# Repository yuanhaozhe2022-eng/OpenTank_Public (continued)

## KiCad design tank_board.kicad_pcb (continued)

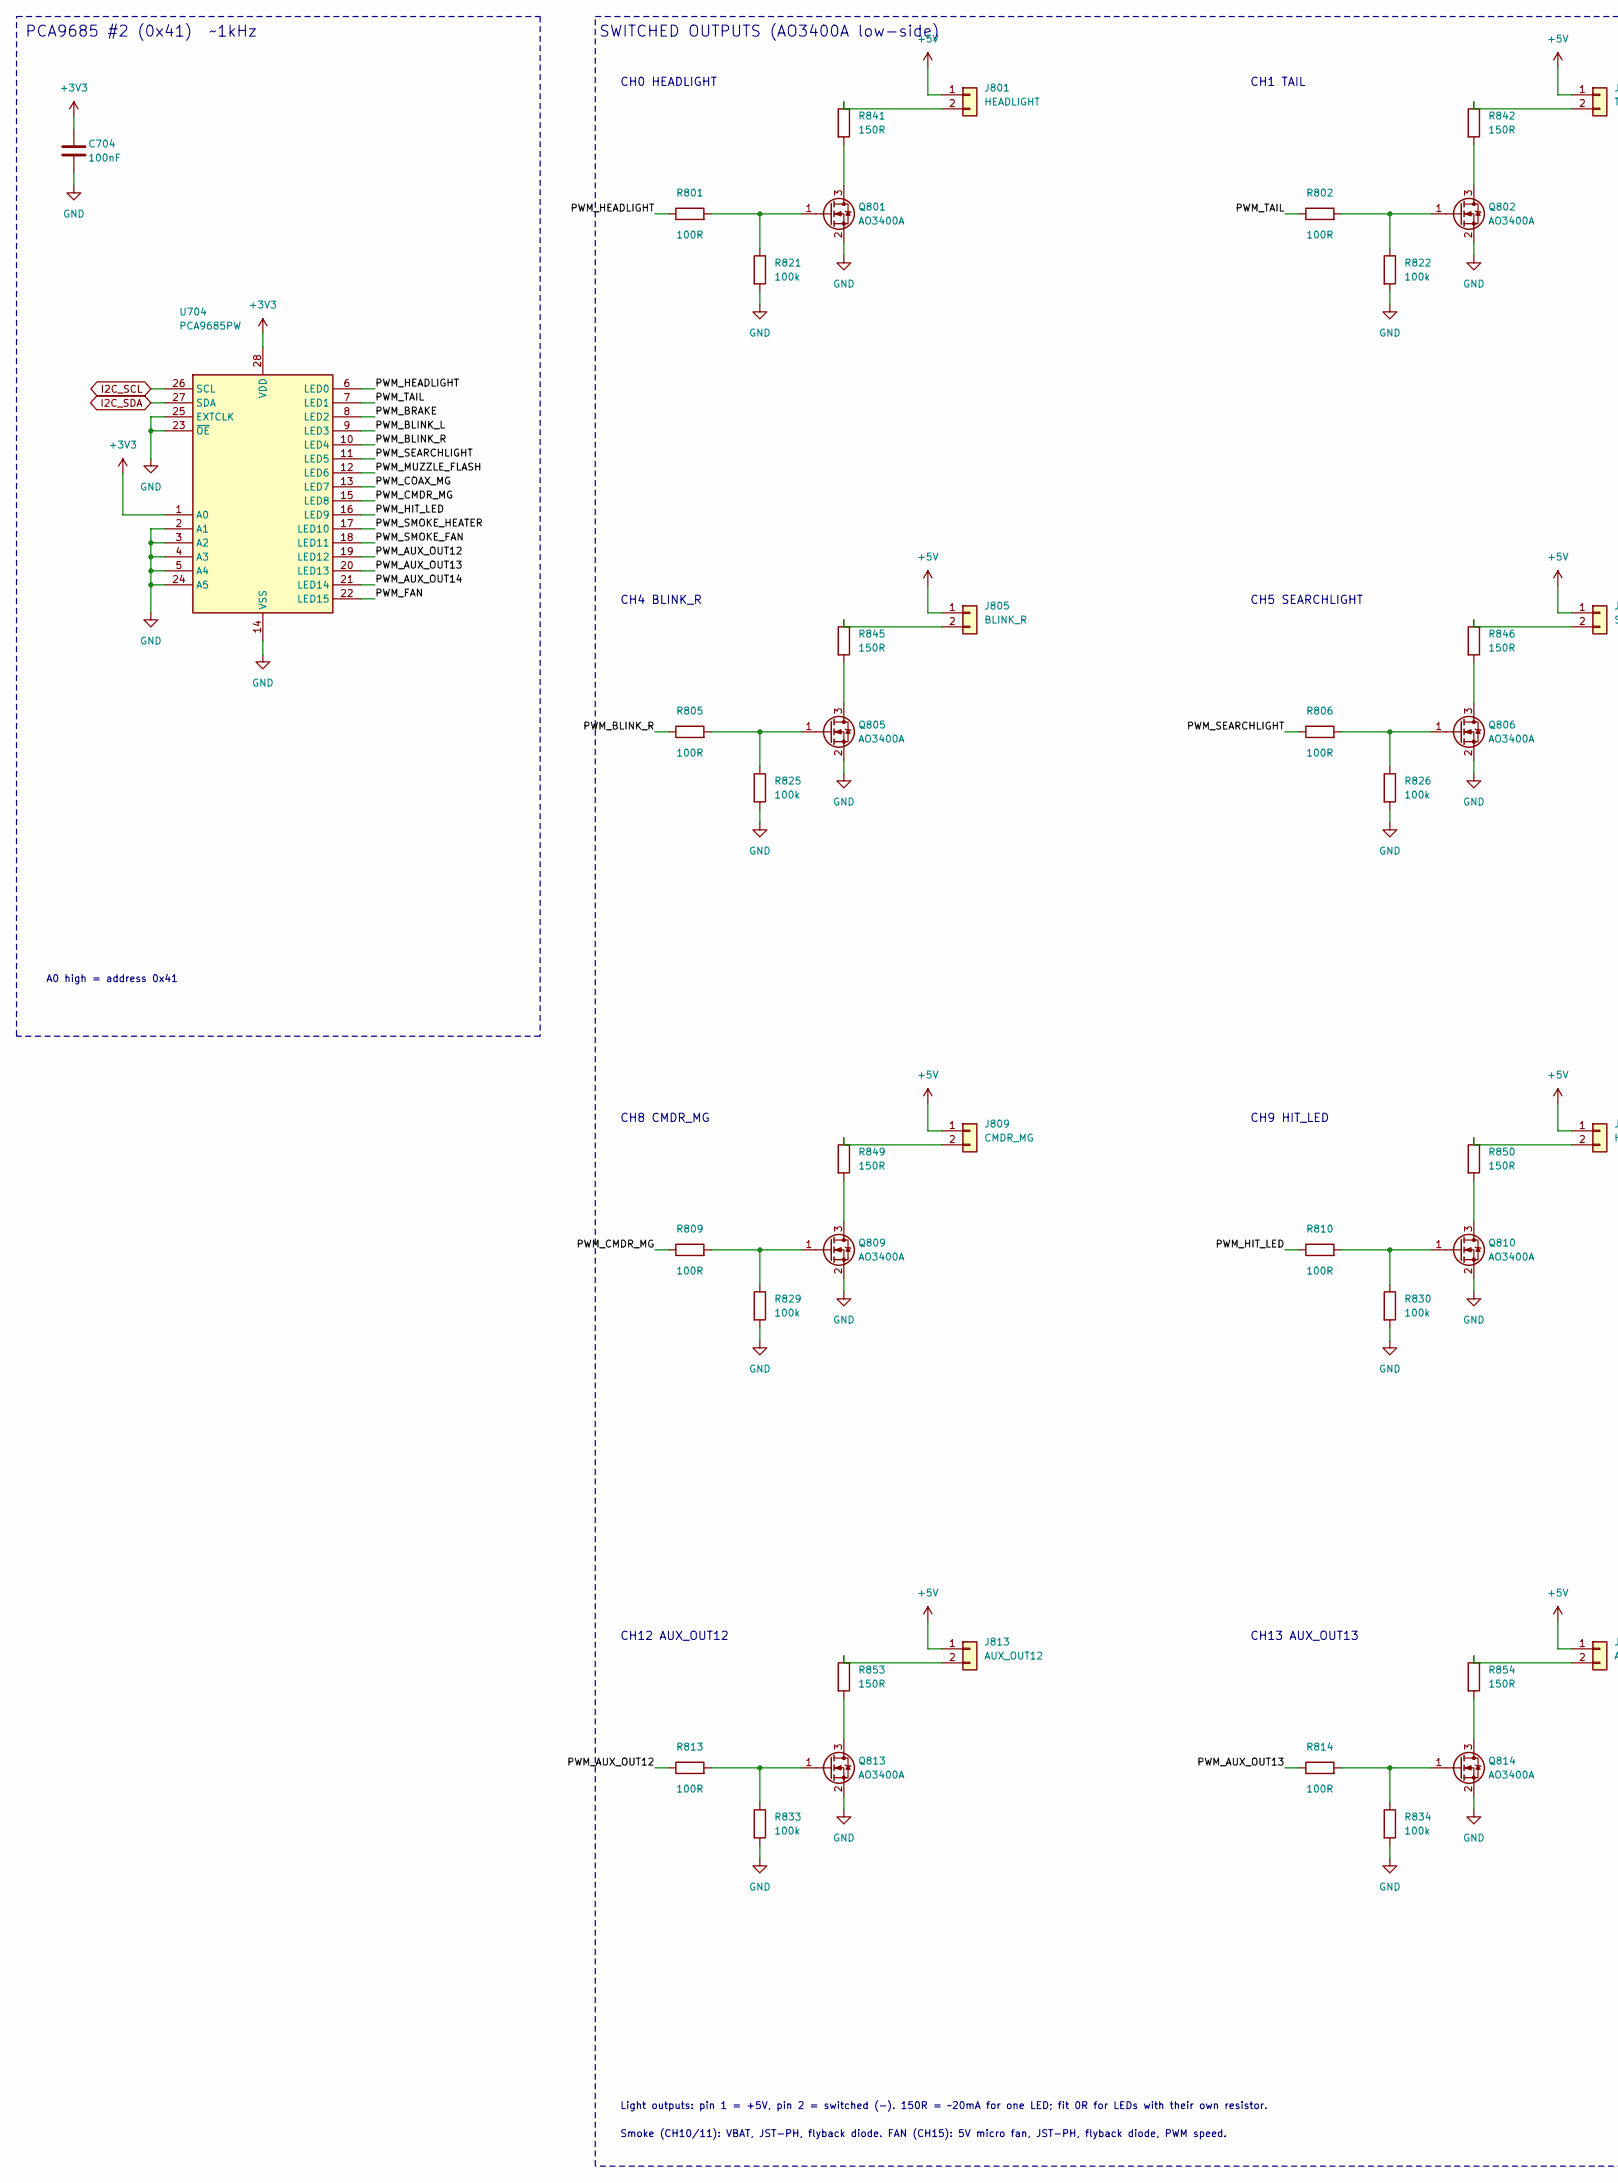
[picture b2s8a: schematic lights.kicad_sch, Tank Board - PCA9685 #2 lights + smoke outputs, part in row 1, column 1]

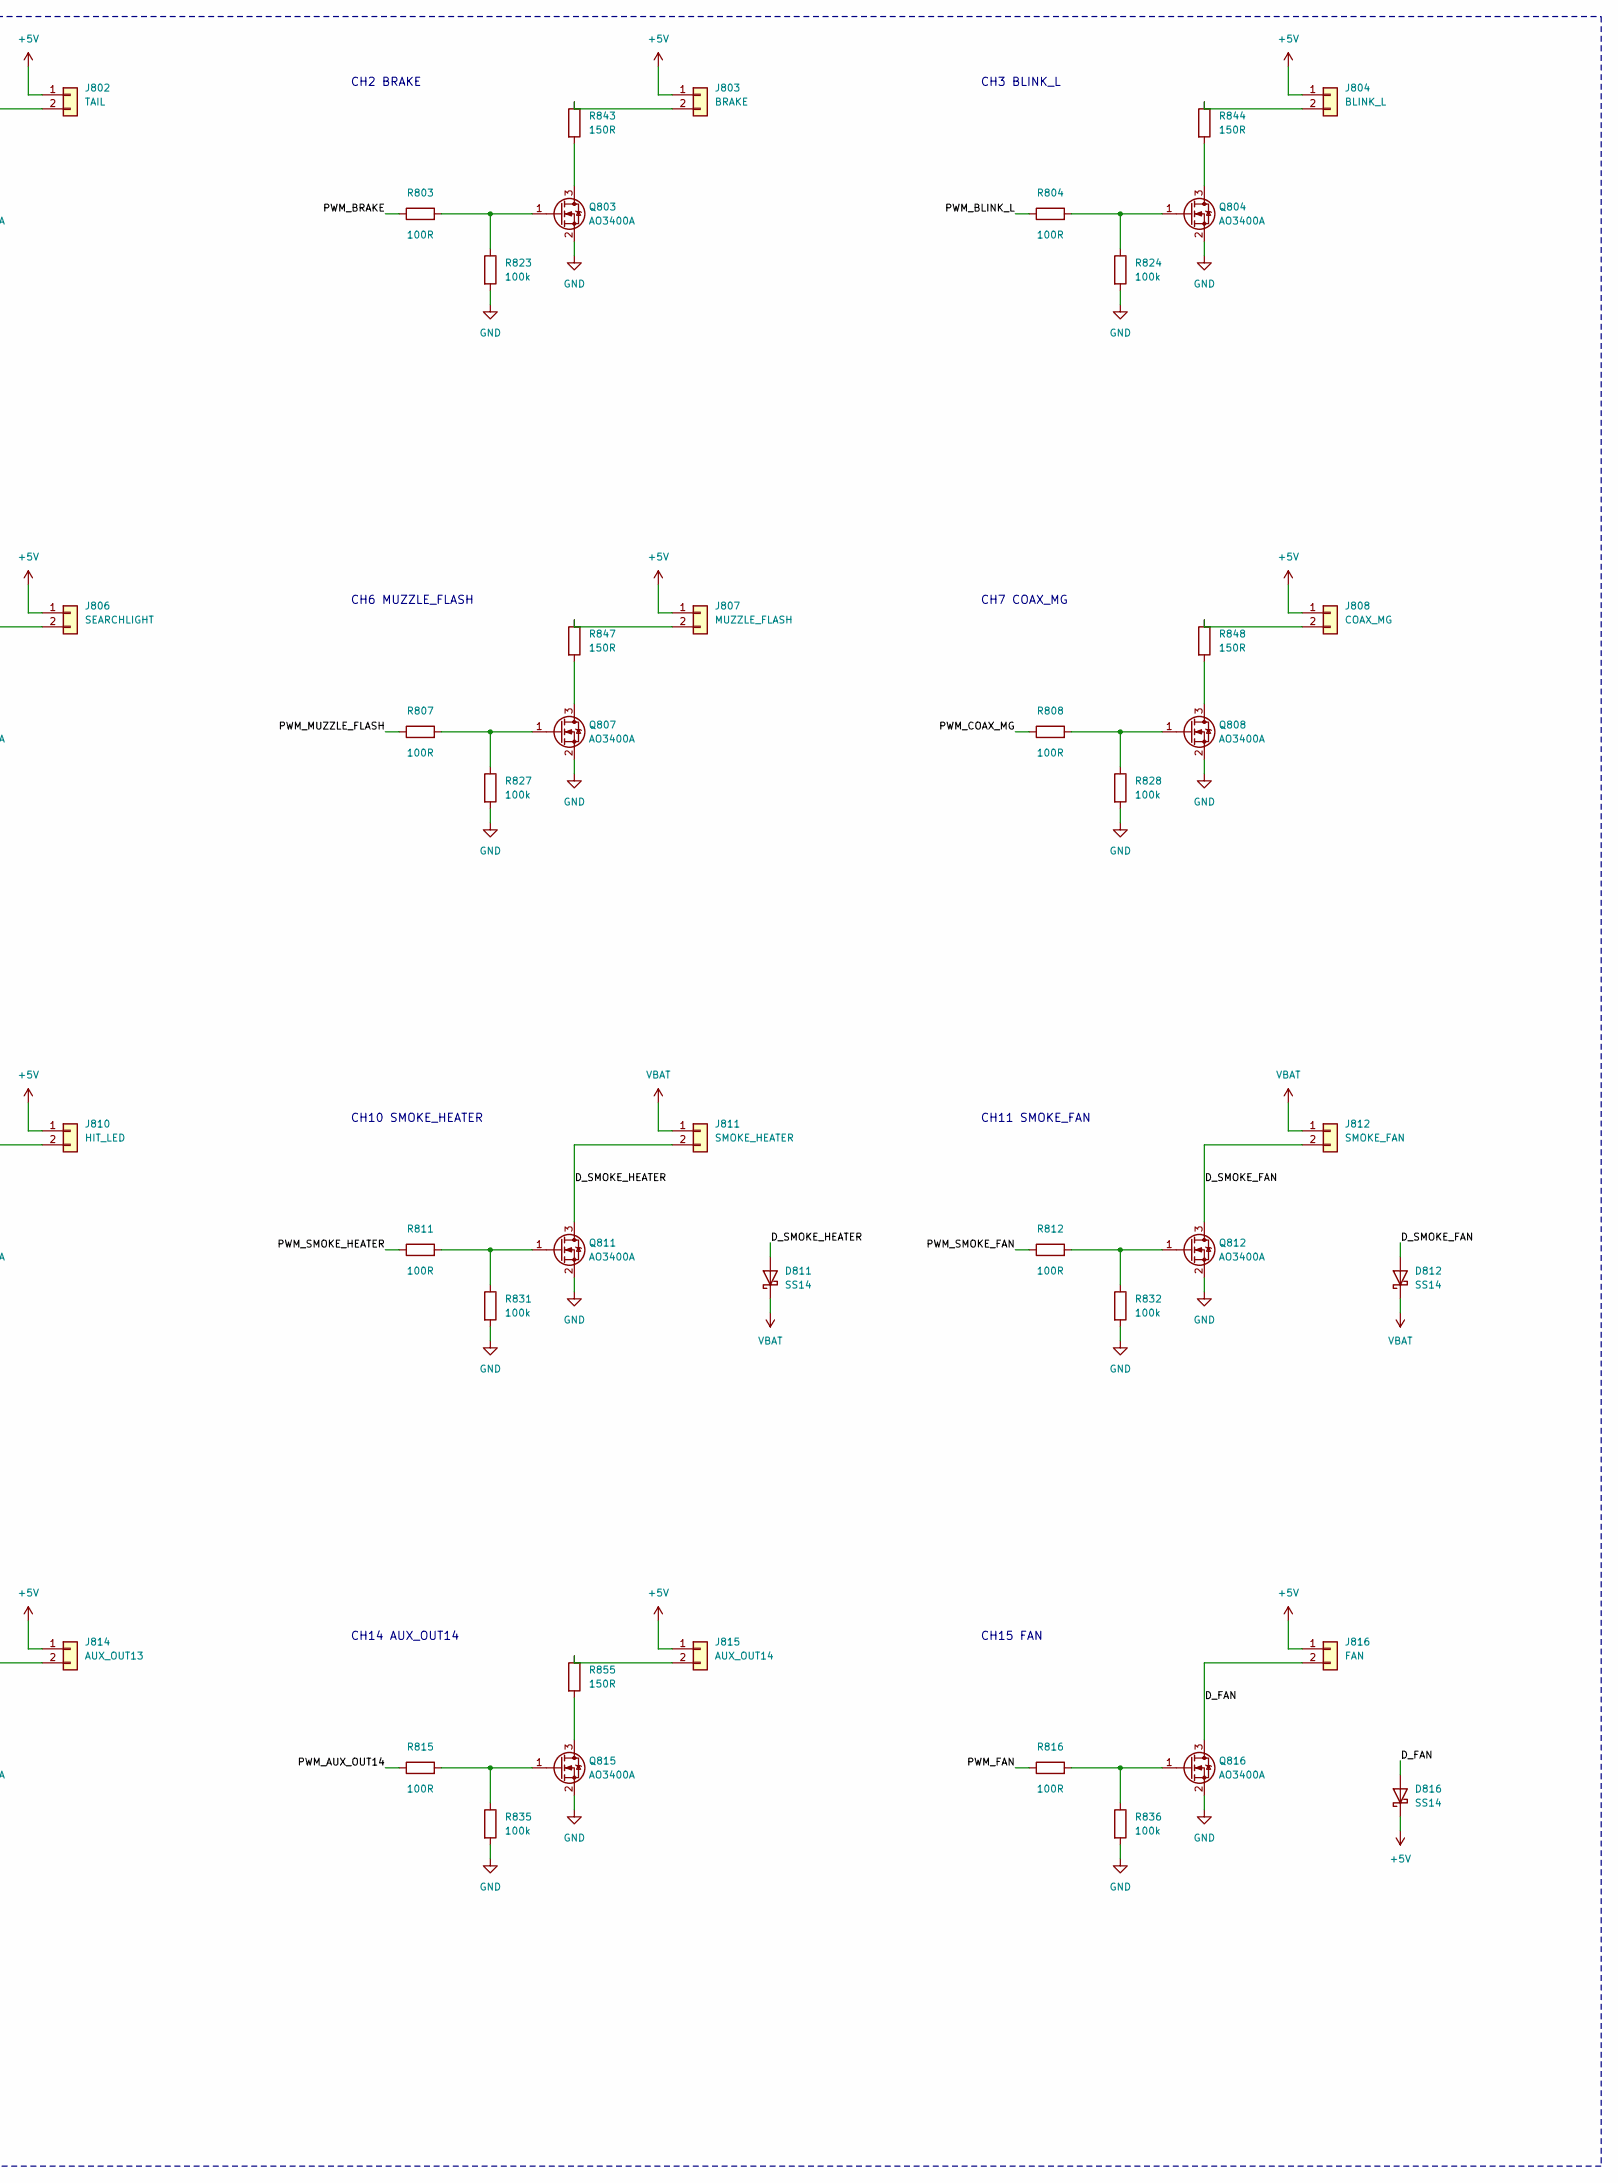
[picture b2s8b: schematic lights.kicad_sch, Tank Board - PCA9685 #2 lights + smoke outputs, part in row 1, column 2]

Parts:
C704: 100nF; C_0603_1608Metric
D811, D812, D816: SS14; D_SOD-123F; MPN SS14 / B140
J801: HEADLIGHT; PinHeader_1x02_P2.54mm_Vertical
J802: TAIL; PinHeader_1x02_P2.54mm_Vertical
J803: BRAKE; PinHeader_1x02_P2.54mm_Vertical
J804: BLINK_L; PinHeader_1x02_P2.54mm_Vertical
J805: BLINK_R; PinHeader_1x02_P2.54mm_Vertical
J806: SEARCHLIGHT; PinHeader_1x02_P2.54mm_Vertical
J807: MUZZLE_FLASH; PinHeader_1x02_P2.54mm_Vertical
J808: COAX_MG; PinHeader_1x02_P2.54mm_Vertical
J809: CMDR_MG; PinHeader_1x02_P2.54mm_Vertical
J810: HIT_LED; PinHeader_1x02_P2.54mm_Vertical
J811: SMOKE_HEATER; JST_PH_B2B-PH-K_1x02_P2.00mm_Vertical
J812: SMOKE_FAN; JST_PH_B2B-PH-K_1x02_P2.00mm_Vertical
J813: AUX_OUT12; PinHeader_1x02_P2.54mm_Vertical
J814: AUX_OUT13; PinHeader_1x02_P2.54mm_Vertical
J815: AUX_OUT14; PinHeader_1x02_P2.54mm_Vertical
J816: FAN; JST_PH_B2B-PH-K_1x02_P2.00mm_Vertical
Q801, Q802, Q803, Q804, Q805, Q806, Q807, Q808, Q809, Q810, Q811, Q812, Q813, Q814, Q815, Q816: AO3400A; SOT-23; MPN AO3400A
R801, R802, R803, R804, R805, R806, R807, R808, R809, R810, R811, R812, R813, R814, R815, R816: 100R; R_0603_1608Metric
R821, R822, R823, R824, R825, R826, R827, R828, R829, R830, R831, R832, R833, R834, R835, R836: 100k; R_0603_1608Metric
R841, R842, R843, R844, R845, R846, R847, R848, R849, R850, R853, R854, R855: 150R; R_0603_1608Metric
U704: PCA9685PW; TSSOP-28_4.4x9.7mm_P0.65mm; MPN PCA9685PW,118

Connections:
+3V3: C704.1, U704.1 (A0), U704.28 (VDD); also elsewhere on the board
+5V: D816.1 (K), J801.1, J802.1, J803.1, J804.1, J805.1, J806.1, J807.1, J808.1, J809.1, J810.1, J813.1, J814.1, J815.1, J816.1; also elsewhere on the board
/Lights/D_FAN: D816.2 (A), J816.2, Q816.3 (D)
/Lights/D_SMOKE_FAN: D812.2 (A), J812.2, Q812.3 (D)
/Lights/D_SMOKE_HEATER: D811.2 (A), J811.2, Q811.3 (D)
/Lights/PWM_AUX_OUT12: R813.1, U704.19 (LED12)
/Lights/PWM_AUX_OUT13: R814.1, U704.20 (LED13)
/Lights/PWM_AUX_OUT14: R815.1, U704.21 (LED14)
/Lights/PWM_BLINK_L: R804.1, U704.9 (LED3)
/Lights/PWM_BLINK_R: R805.1, U704.10 (LED4)
/Lights/PWM_BRAKE: R803.1, U704.8 (LED2)
/Lights/PWM_CMDR_MG: R809.1, U704.15 (LED8)
/Lights/PWM_COAX_MG: R808.1, U704.13 (LED7)
/Lights/PWM_FAN: R816.1, U704.22 (LED15)
/Lights/PWM_HEADLIGHT: R801.1, U704.6 (LED0)
/Lights/PWM_HIT_LED: R810.1, U704.16 (LED9)
/Lights/PWM_MUZZLE_FLASH: R807.1, U704.12 (LED6)
/Lights/PWM_SEARCHLIGHT: R806.1, U704.11 (LED5)
/Lights/PWM_SMOKE_FAN: R812.1, U704.18 (LED11)
/Lights/PWM_SMOKE_HEATER: R811.1, U704.17 (LED10)
/Lights/PWM_TAIL: R802.1, U704.7 (LED1)
GND: C704.2, Q801.2 (S), Q802.2 (S), Q803.2 (S), Q804.2 (S), Q805.2 (S), Q806.2 (S), Q807.2 (S), Q808.2 (S), Q809.2 (S), Q810.2 (S), Q811.2 (S), Q812.2 (S), Q813.2 (S), Q814.2 (S), Q815.2 (S), Q816.2 (S), R821.2, R822.2, R823.2, R824.2, R825.2, R826.2, R827.2, R828.2, R829.2, R830.2, R831.2, R832.2, R833.2, R834.2, R835.2, R836.2, U704.2 (A1), U704.3 (A2), U704.4 (A3), U704.5 (A4), U704.14 (VSS), U704.23 (~OE), U704.24 (A5), U704.25 (EXTCLK); also elsewhere on the board
I2C_SCL: U704.26 (SCL); also elsewhere on the board
I2C_SDA: U704.27 (SDA); also elsewhere on the board
unnamed: J801.2, R841.1
unnamed: J802.2, R842.1
unnamed: J803.2, R843.1
unnamed: J804.2, R844.1
unnamed: J805.2, R845.1
unnamed: J806.2, R846.1
unnamed: J807.2, R847.1
unnamed: J808.2, R848.1
unnamed: J809.2, R849.1
unnamed: J810.2, R850.1
unnamed: J813.2, R853.1
unnamed: J814.2, R854.1
unnamed: J815.2, R855.1
unnamed: Q801.3 (D), R841.2
unnamed: Q801.1 (G), R801.2, R821.1
unnamed: Q802.3 (D), R842.2
unnamed: Q802.1 (G), R802.2, R822.1
unnamed: Q803.3 (D), R843.2
unnamed: Q803.1 (G), R803.2, R823.1
unnamed: Q804.3 (D), R844.2
unnamed: Q804.1 (G), R804.2, R824.1
unnamed: Q805.3 (D), R845.2
unnamed: Q805.1 (G), R805.2, R825.1
unnamed: Q806.3 (D), R846.2
unnamed: Q806.1 (G), R806.2, R826.1
unnamed: Q807.3 (D), R847.2
unnamed: Q807.1 (G), R807.2, R827.1
unnamed: Q808.3 (D), R848.2
unnamed: Q808.1 (G), R808.2, R828.1
unnamed: Q809.3 (D), R849.2
unnamed: Q809.1 (G), R809.2, R829.1
unnamed: Q810.3 (D), R850.2
unnamed: Q810.1 (G), R810.2, R830.1
unnamed: Q811.1 (G), R811.2, R831.1
unnamed: Q812.1 (G), R812.2, R832.1
unnamed: Q813.3 (D), R853.2
unnamed: Q813.1 (G), R813.2, R833.1
unnamed: Q814.3 (D), R854.2
unnamed: Q814.1 (G), R814.2, R834.1
unnamed: Q815.3 (D), R855.2
unnamed: Q815.1 (G), R815.2, R835.1
unnamed: Q816.1 (G), R816.2, R836.1
VBAT: D811.1 (K), D812.1 (K), J811.1, J812.1; also elsewhere on the board

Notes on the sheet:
PCA9685 #2 (0x41) ~1kHz
A0 high = address 0x41
SWITCHED OUTPUTS (AO3400A low-side)
CH0 HEADLIGHT
CH1 TAIL
CH2 BRAKE
CH3 BLINK_L
CH4 BLINK_R
CH5 SEARCHLIGHT
CH6 MUZZLE_FLASH
CH7 COAX_MG
CH8 CMDR_MG
CH9 HIT_LED
CH10 SMOKE_HEATER
CH11 SMOKE_FAN
CH12 AUX_OUT12
CH13 AUX_OUT13
CH14 AUX_OUT14
CH15 FAN
Light outputs: pin 1 = +5V, pin 2 = switched (-). 150R = ~20mA for one LED; fit 0R for LEDs with their own resistor.
Smoke (CH10/11): VBAT, JST-PH, flyback diode. FAN (CH15): 5V micro fan, JST-PH, flyback diode, PWM speed.

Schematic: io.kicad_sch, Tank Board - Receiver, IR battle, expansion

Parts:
C901: 4.7uF; C_0805_2012Metric
J901: RECEIVER (RX TX + -); PinHeader_1x04_P2.54mm_Vertical
J902: IR LED (A K); PinHeader_1x02_P2.54mm_Vertical
J903: IR RECEIVER (OUT + -); PinHeader_1x03_P2.54mm_Vertical
J904: EXPANSION (7 8 42 45 3V3 5V - -); PinHeader_2x04_P2.54mm_Vertical
Q901: AO3400A; SOT-23; MPN AO3400A
R901: 1k; R_0603_1608Metric
R902: 220R; R_0603_1608Metric
R903, R906: 100R; R_0603_1608Metric
R904: 100k; R_0603_1608Metric
R905: 33R 1/4W; R_1206_3216Metric
R907: 10k; R_0603_1608Metric
R908, R910, R911, R912, R913: 330R; R_0603_1608Metric

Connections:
+3V3: J904.5, R906.1, R907.1; also elsewhere on the board
+5V: J901.3, J904.6, R905.1; also elsewhere on the board
/Receiver_IR_Exp/EXP7: J904.1, R910.2
/Receiver_IR_Exp/EXP8: J904.2, R911.2
/Receiver_IR_Exp/EXP42: J904.3, R912.2
/Receiver_IR_Exp/EXP45: J904.4, R913.2
/Receiver_IR_Exp/IR_G: Q901.1 (G), R903.2, R904.1
/Receiver_IR_Exp/IR_LED_A: J902.1, R905.2
/Receiver_IR_Exp/IR_LED_K: J902.2, Q901.3 (D)
/Receiver_IR_Exp/IR_RX_OUT: J903.1, R907.2, R908.2
/Receiver_IR_Exp/IR_VS: C901.1, J903.2, R906.2
/Receiver_IR_Exp/RCV_IN: J901.2, R902.2
/Receiver_IR_Exp/RCV_OUT: J901.1, R901.2
EXP_GPIO7: R910.1; also elsewhere on the board
EXP_GPIO8: R911.1; also elsewhere on the board
EXP_GPIO42: R912.1; also elsewhere on the board
EXP_GPIO45: R913.1; also elsewhere on the board
GND: C901.2, J901.4, J903.3, J904.7, J904.8, Q901.2 (S), R904.2; also elsewhere on the board
IR_RX: R908.1; also elsewhere on the board
IR_TX: R903.1; also elsewhere on the board
RX_UART_RX: R901.1; also elsewhere on the board
RX_UART_TX: R902.1; also elsewhere on the board

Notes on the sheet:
RECEIVER (SBUS / iBUS / PPM / CRSF-ELRS)
1k on the input limits current if a receiver outputs 5V PPM (ESP32 is 3.3V only).
SBUS inversion done in the ESP32 UART - no inverter needed. PWM-only RX: use a PWM->PPM encoder.
IR BATTLE (Tamiya / Heng Long compatible, 38kHz)
100k pull-down keeps GPIO46 (strapping pin) low at boot.
Receiver supply RC filter per Vishay TSOP app note.
EXPANSION (secondary turret board, sensors, whatever)
GPIO7/8 = UART (TX/RX) for a 2nd turret board or another ESP32.
GPIO42 = general I/O. GPIO45 = OUTPUT ONLY (strapping pin, must stay low at boot).
All 4 have 330R series protection. 3.3V logic only - never feed 5V into them.
More I/O: MCP23017 header (expander sheet), spare servo CH5-15, Qwiic ports.

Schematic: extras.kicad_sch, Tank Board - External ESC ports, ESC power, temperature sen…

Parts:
C1001: 100nF; C_0603_1608Metric
J1001: ESC1 turret rotation (S nc -); PinHeader_1x03_P2.54mm_Vertical
J1002: ESC2 gun elevation (S nc -); PinHeader_1x03_P2.54mm_Vertical
J1003: ESC3 (CH14) (S nc -); PinHeader_1x03_P2.54mm_Vertical
J1004: ESC4 (CH15) (S nc -); PinHeader_1x03_P2.54mm_Vertical
J1005: ESC POWER 1 (VBAT -); AMASS_XT30U-F_1x02_P5.0mm_Vertical; MPN AMASS XT30U-F
J1006: ESC POWER 2 (VBAT -); AMASS_XT30U-F_1x02_P5.0mm_Vertical; MPN AMASS XT30U-F
R1001, R1002, R1003, R1004: 220R; R_0603_1608Metric
U1001: TMP1075DGK; VSSOP-8_3.0x3.0mm_P0.65mm; MPN TMP1075DGKR

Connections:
+3V3: C1001.1, U1001.8 (V+); also elsewhere on the board
/Extras/ESC1_SIG: J1001.1, R1001.2
/Extras/ESC2_SIG: J1002.1, R1002.2
/Extras/ESC3_SIG: J1003.1, R1003.2
/Extras/ESC4_SIG: J1004.1, R1004.2
GND: C1001.2, J1001.3, J1002.3, J1003.3, J1004.3, J1005.2, J1006.2, U1001.4 (GND), U1001.5 (A2), U1001.6 (A1), U1001.7 (A0); also elsewhere on the board
I2C_SCL: U1001.2 (SCL); also elsewhere on the board
I2C_SDA: U1001.1 (SDA); also elsewhere on the board
SERVO_PWM14: R1003.1; also elsewhere on the board
SERVO_PWM15: R1004.1; also elsewhere on the board
TUR_ELEV_SERVO: R1002.1; also elsewhere on the board
TUR_ROT_SERVO: R1001.1; also elsewhere on the board
VBAT: J1005.1, J1006.1; also elsewhere on the board

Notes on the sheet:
EXTERNAL ESC PORTS (signal + GND only, BEC pin left open)
Signal = normal 50Hz servo pulse from the PCA9685. ESC1/2 share the turret servo channels (CH0/CH1),
ESC3/4 share spare servo CH14/CH15 - use the servo header OR the ESC port on a channel, not both.
Power the ESCs from the XT30 outputs below (battery voltage, after fuse + reverse protection).
ESC POWER OUT 2x XT30 (each feeds 2 ESCs with a Y-lead)
Shares the main 15A fuse with everything else. Turret ESCs draw little - just no 4x full-stall.
DRIVER TEMPERATURE TMP1075 (I2C 0x48)
A0-A2 = GND -> address 0x48 (no clash with 0x20/0x40/0x41).
Firmware reads it and runs the FAN output (lights CH15) when the drivers get warm.

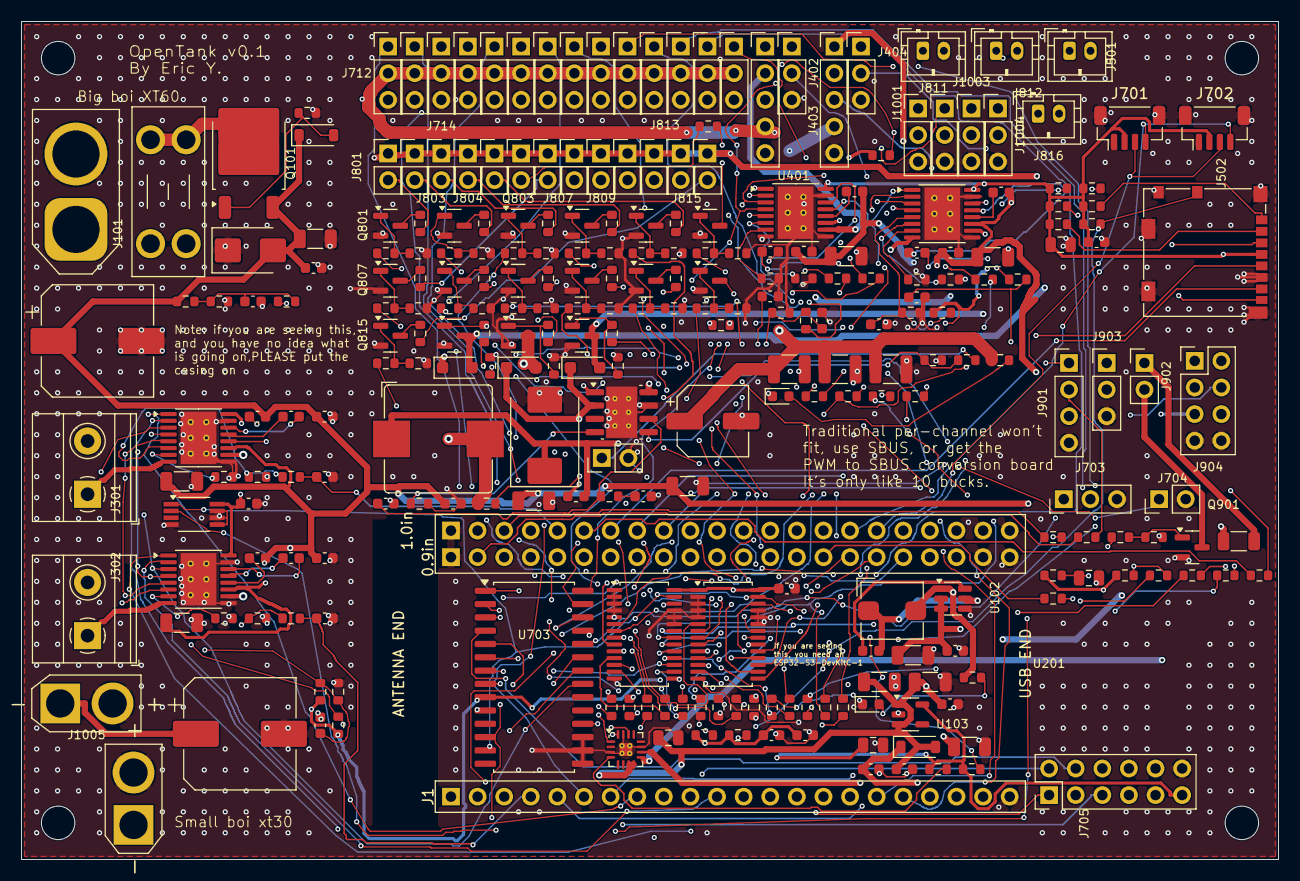
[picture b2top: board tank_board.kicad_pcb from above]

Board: 4 copper layers, 120.0 x 80.0 mm, 276 parts (0 on the bottom side), 214 nets.
